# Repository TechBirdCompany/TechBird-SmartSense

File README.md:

# Introduction
TechBird-SmartSense is an IoT device with a 4-channel 12-Bit ADC, to measure up to 4 temperatures. In addition it also provides an internal temperature sensore for ambiant temperatures.

# Features
- ESP32-C6-MINI-1-N4: As module
- EEMB LP103454: 2000 mAh Lipo Battery
  - 7 days of uptime with 10 seconds time gab, and ringbuffer size of 60
- ADS1015IDGSR: 2 Differntiall or 4 Channel 12-Bit ADC
- FM24CL64B-GTR: 64 kB FRAM
- RV-3028-C7: Internal RTC
- TMP1075D: Internal Temperature Sensor
- USB Type-C for communication and charging

# Software
- Use at your own risk!
- Basic UI via USB (115200, 8, n, 1)
- Sending Data via MQTT
- Again... use at your own risk!
- Bugs are free to find, and free to fix.

# Known Bugs
## Hardware
- For some reasons, unknown to men, the LiPo Battery is necessary, to provide enough energy for initial W-LAN connection. Or maybe use a beefier USB power supply
- <span style="text-decoration:overline">WKUP</span> need to be routed to IO2

## Software
- When ringbuffer loops, one set of wrong data will be send

# Known Nuisances
- When in deep sleep, attaching USB connection won't reset the device and the lid need to be removed in order to get to the bootmenu
- Main connector is not made to be removed frequently, which makes charging pretty annoying

# Arduino IDE Setup
- The settings should look something like this:

- The following libraries shoulld be installed:
  - https://github.com/arduino-libraries/Arduino_JSON
  - https://github.com/arduino-libraries/NTPClient
  - https://github.com/adafruit/Adafruit_ADS1X15
  - https://github.com/hideakitai/DebugLog
  - https://github.com/RobTillaart/FRAM_I2C
  - https://github.com/256dpi/arduino-mqtt
  - https://github.com/constiko/RV-3028_C7-Arduino_Library
  - https://github.com/PatrickBaus/Arduino-TMP1075/tree/master
    - Needs to be installed manually

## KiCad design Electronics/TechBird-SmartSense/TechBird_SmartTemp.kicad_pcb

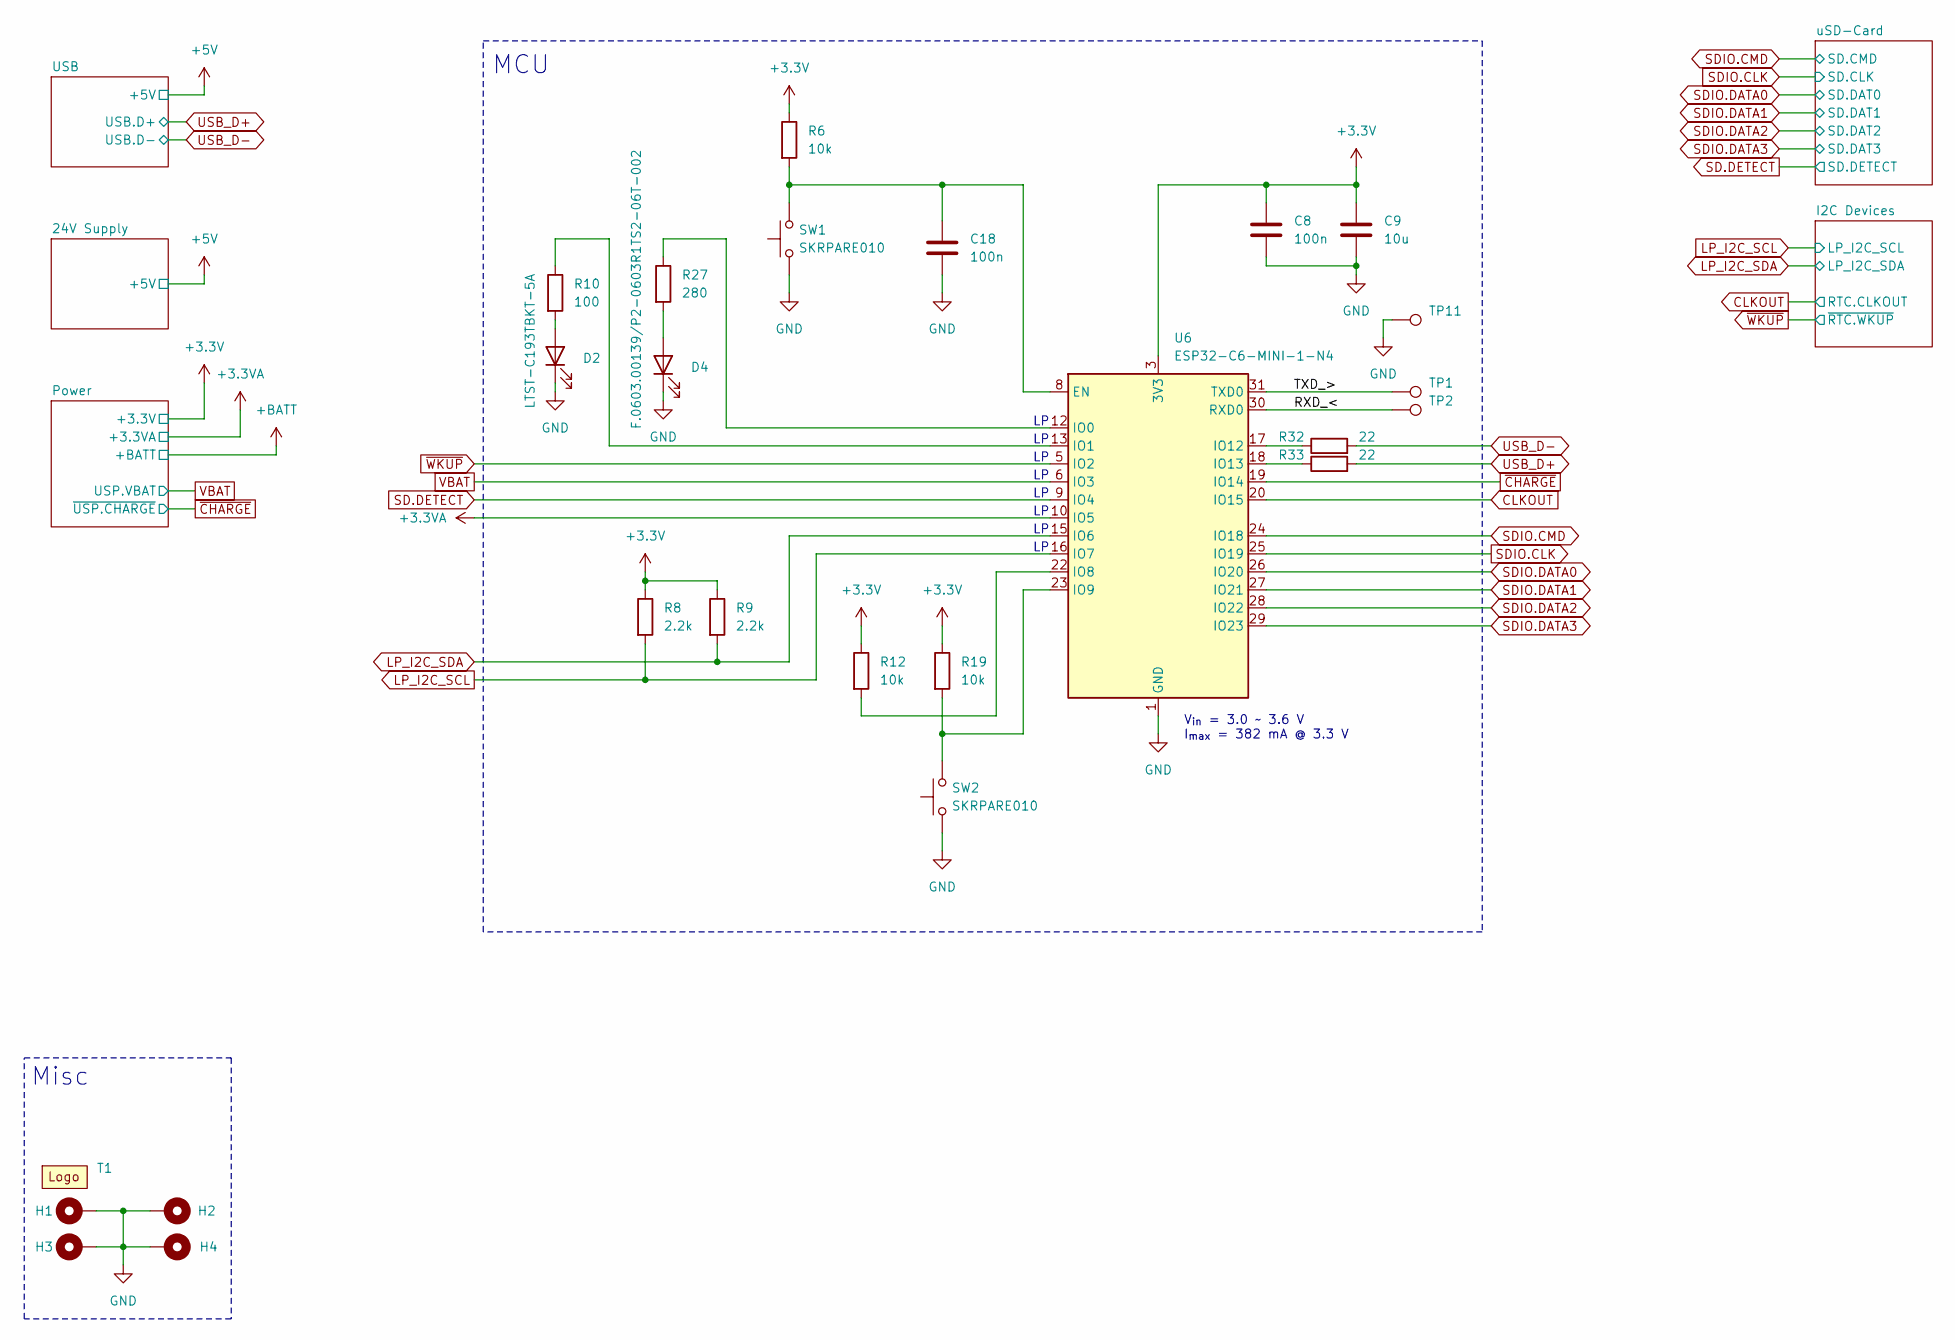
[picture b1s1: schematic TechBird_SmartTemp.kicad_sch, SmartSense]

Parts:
C8, C18: 100n; C_0603_1608Metric; MFG# C0603C104K3RACTU; DigiKey 399-C0603C104K3RACTUCT-ND
C9: 10u; C_0603_1608Metric; MFG# LMK107BBJ106MALT; DigiKey 587-3258-1-ND
D2: LTST-C193TBKT-5A; LED_0603_1608Metric; MFG# LTST-C193TBKT-5A; DigiKey 160-1827-1-ND
D4: F.0603.00139/P2-0603R1TS2-06T-002; LED_0603_1608Metric; MFG# F.0603.00139/P2-0603R1TS2-06T-002
H1, H2, H3, H4: MountingHole_Pad; MountingHole_3.2mm_M3_DIN965_Pad
R6, R12, R19: 10k; R_0603_1608Metric; MFG# RC0603FR-0710KL; DigiKey 311-10.0KHRCT-ND
R8, R9: 2.2k; R_0603_1608Metric; MFG# CRGCQ0603F2K2; DigiKey A129692CT-ND
R10: 100; R_0603_1608Metric; MFG# CRCW0603100RFKEA; DigiKey 541-100HCT-ND
R27: 280; R_0603_1608Metric; MFG# RC0603FR-07280RL; DigiKey 311-280HRCT-ND
R32, R33: 22; R_0603_1608Metric; MFG# RMCF0603FT22R0; DigiKey RMCF0603FT22R0CT-ND
SW1, SW2: SKRPARE010; SW_Push_1P1T_NO_Vertical_Wuerth_434133025816; MFG# SKRPARE010; DigiKey 4809-SKRPARE010CT-ND
T1: TechBird_Silk
TP1, TP2, TP11: TestPoint; TestPoint_Pad_D1.0mm
U6: ESP32-C6-MINI-1-N4; ESP32-C6-MINI-1; MFG# ESP32-C6-MINI-1-N4; DigiKey 1965-ESP32-C6-MINI-1-N4CT-ND

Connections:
+3.3V: C8.1, C9.1, R6.1, R8.1, R9.1, R12.1, R19.1, U6.3 (3V3); also elsewhere on the board
+3.3VA: U6.10 (IO5); also elsewhere on the board
/RXD_<: TP2.1, U6.30 (RXD0)
/TXD_>: TP1.1, U6.31 (TXD0)
CLKOUT: U6.20 (IO15); also elsewhere on the board
GND: C8.2, C9.2, C18.2, D2.1 (K), D4.1 (K), H1.1, H2.1, H3.1, H4.1, SW1.1, SW2.1, TP11.1, U6.1 (GND), U6.2 (GND), U6.11 (GND), U6.14 (GND), U6.36 (GND), U6.37 (GND), U6.38 (GND), U6.39 (GND), U6.40 (GND), U6.41 (GND), U6.42 (GND), U6.43 (GND), U6.44 (GND), U6.45 (GND), U6.46 (GND), U6.47 (GND), U6.48 (GND), U6.49 (GND), U6.50 (GND), U6.51 (GND), U6.52 (GND), U6.53 (GND); also elsewhere on the board
LP_I2C_SCL: R8.2, U6.16 (IO7); also elsewhere on the board
LP_I2C_SDA: R9.2, U6.15 (IO6); also elsewhere on the board
unnamed: D2.2 (A), R10.2
unnamed: D4.2 (A), R27.2
unnamed: C18.1, R6.2, SW1.2, U6.8 (EN)
unnamed: R27.1, U6.12 (IO0)
unnamed: R10.1, U6.13 (IO1)
unnamed: R12.2, U6.22 (IO8)
unnamed: R19.2, SW2.2, U6.23 (IO9)
unnamed: R32.1, U6.17 (IO12)
unnamed: R33.1, U6.18 (IO13)
SD.DETECT: U6.9 (IO4); also elsewhere on the board
SDIO.CLK: U6.25 (IO19); also elsewhere on the board
SDIO.CMD: U6.24 (IO18); also elsewhere on the board
SDIO.DATA0: U6.26 (IO20); also elsewhere on the board
SDIO.DATA1: U6.27 (IO21); also elsewhere on the board
SDIO.DATA2: U6.28 (IO22); also elsewhere on the board
SDIO.DATA3: U6.29 (IO23); also elsewhere on the board
USB_D+: R33.2; also elsewhere on the board
USB_D-: R32.2; also elsewhere on the board
VBAT: U6.6 (IO3); also elsewhere on the board
~CHARGE: U6.19 (IO14); also elsewhere on the board
~WKUP: U6.5 (IO2); also elsewhere on the board

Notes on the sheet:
Misc
V_{in} = 3.0 ~ 3.6 V I_{max} = 382 mA @ 3.3 V
MCU

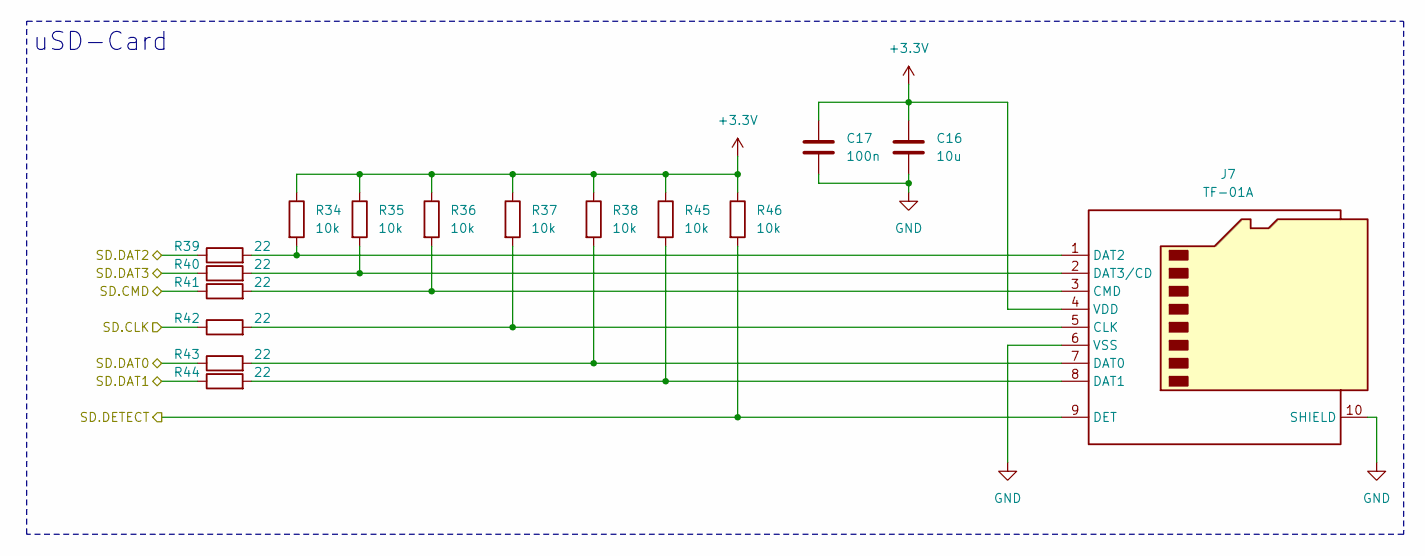
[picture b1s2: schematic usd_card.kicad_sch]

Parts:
C16: 10u; C_0603_1608Metric; MFG# LMK107BBJ106MALT; DigiKey 587-3258-1-ND
C17: 100n; C_0603_1608Metric; MFG# C0603C104K3RACTU; DigiKey 399-C0603C104K3RACTUCT-ND
J7: TF-01A; HRO TF-01A
R34, R35, R36, R37, R38, R45, R46: 10k; R_0603_1608Metric; MFG# RC0603FR-0710KL; DigiKey 311-10.0KHRCT-ND
R39, R40, R41, R42, R43, R44: 22; R_0603_1608Metric; MFG# RMCF0603FT22R0; DigiKey RMCF0603FT22R0CT-ND

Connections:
+3.3V: C16.1, C17.1, J7.4 (VDD), R34.1, R35.1, R36.1, R37.1, R38.1, R45.1, R46.1; also elsewhere on the board
GND: C16.2, C17.2, J7.6 (VSS), J7.10 (SHIELD); also elsewhere on the board
unnamed: J7.5 (CLK), R37.2, R42.2
unnamed: J7.3 (CMD), R36.2, R41.2
unnamed: J7.7 (DAT0), R38.2, R43.2
unnamed: J7.8 (DAT1), R44.2, R45.2
unnamed: J7.1 (DAT2), R34.2, R39.2
unnamed: J7.2 (DAT3/CD), R35.2, R40.2
SD.DETECT: J7.9 (DET), R46.2; also elsewhere on the board
SDIO.CLK: R42.1; also elsewhere on the board
SDIO.CMD: R41.1; also elsewhere on the board
SDIO.DATA0: R43.1; also elsewhere on the board
SDIO.DATA1: R44.1; also elsewhere on the board
SDIO.DATA2: R39.1; also elsewhere on the board
SDIO.DATA3: R40.1; also elsewhere on the board

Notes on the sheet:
uSD-Card

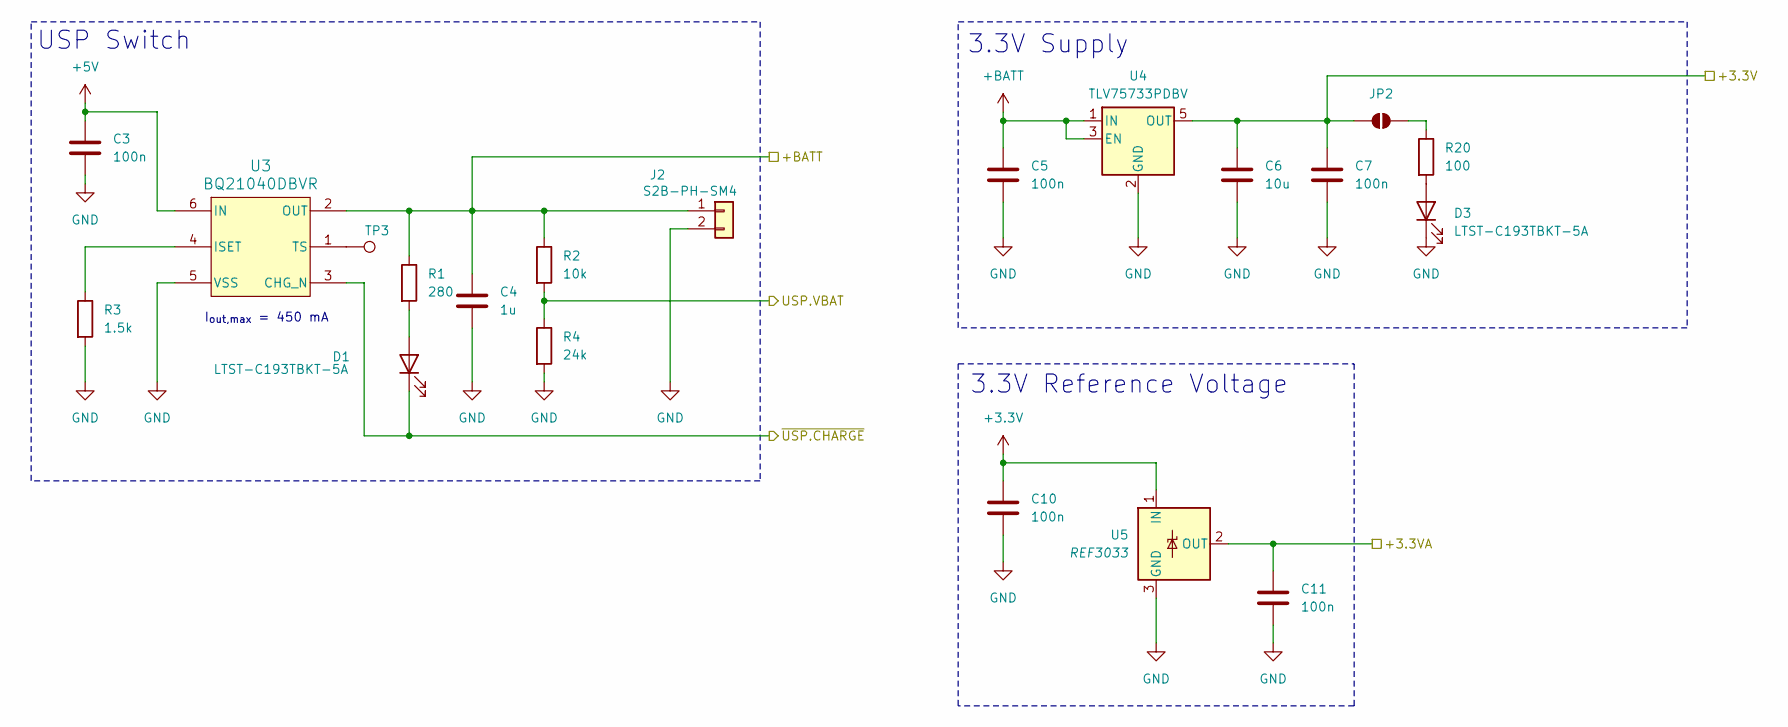
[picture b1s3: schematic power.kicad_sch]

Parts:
C3, C5, C7, C10, C11: 100n; C_0603_1608Metric; MFG# C0603C104K3RACTU; DigiKey 399-C0603C104K3RACTUCT-ND
C4: 1u; C_0603_1608Metric; MFG# C1608X7R1C105K080DC; DigiKey 445-C1608X7R1C105K080DCCT-ND
C6: 10u; C_0603_1608Metric; MFG# LMK107BBJ106MALT; DigiKey 587-3258-1-ND
D1, D3: LTST-C193TBKT-5A; LED_0603_1608Metric; MFG# LTST-C193TBKT-5A; DigiKey 160-1827-1-ND
J2: S2B-PH-SM4; JST_PH_S2B-PH-SM4-TB_1x02-1MP_P2.00mm_Horizontal; MFG# S2B-PH-SM4-TB; DigiKey 455-S2B-PH-SM4-TBCT-ND
JP2: SolderJumper_2_Open; SolderJumper-2_P1.3mm_Open_TrianglePad1.0x1.5mm
R1: 280; R_0603_1608Metric; MFG# ERJ-3EKF2800V; DigiKey P280HCT-ND
R2: 10k; R_0603_1608Metric; MFG# RC0603FR-0710KL; DigiKey 311-10.0KHRCT-ND
R3: 1.5k; R_0603_1608Metric; MFG# ERA-3AEB152V; DigiKey P1.5KDBCT-ND
R4: 24k; R_0603_1608Metric; MFG# CRCW060324K0FKEAC; DigiKey 541-5285-1-ND
R20: 100; R_0603_1608Metric; MFG# CRCW0603100RFKEA; DigiKey 541-100HCT-ND
TP3: TestPoint; TestPoint_Pad_D1.0mm
U3: BQ21040DBVR; SOT-23-6; MFG# BQ21040DBVR; DigiKey 296-47315-1-ND
U4: TLV75733PDBV; SOT-23-5; MFG# TLV75733PDBVR; DigiKey 296-50414-1-ND
U5: REF3033; SOT-23; MFG# REF3033AIDBZR; DigiKey 296-26324-1-ND

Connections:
+3.3V: C6.1, C7.1, C10.1, JP2.2 (B), U4.5 (OUT), U5.1 (IN); also elsewhere on the board
+3.3VA: C11.1, U5.2 (OUT); also elsewhere on the board
+5V: C3.1, U3.6 (IN); also elsewhere on the board
+BATT: C4.1, C5.1, J2.1, R1.1, R2.1, U3.2 (OUT), U4.1 (IN), U4.3 (EN)
GND: C3.2, C4.2, C5.2, C6.2, C7.2, C10.2, C11.2, D3.1 (K), J2.2, R3.2, R4.2, U3.5 (VSS), U4.2 (GND), U5.3 (GND); also elsewhere on the board
unnamed: D1.2 (A), R1.2
unnamed: D3.2 (A), R20.2
unnamed: JP2.1 (A), R20.1
unnamed: R3.1, U3.4 (ISET)
unnamed: TP3.1, U3.1 (TS)
VBAT: R2.2, R4.1; also elsewhere on the board
~CHARGE: D1.1 (K), U3.3 (CHG_N); also elsewhere on the board

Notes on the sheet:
I_{out,max} = 450 mA
USP Switch
3.3V Supply
3.3V Reference Voltage

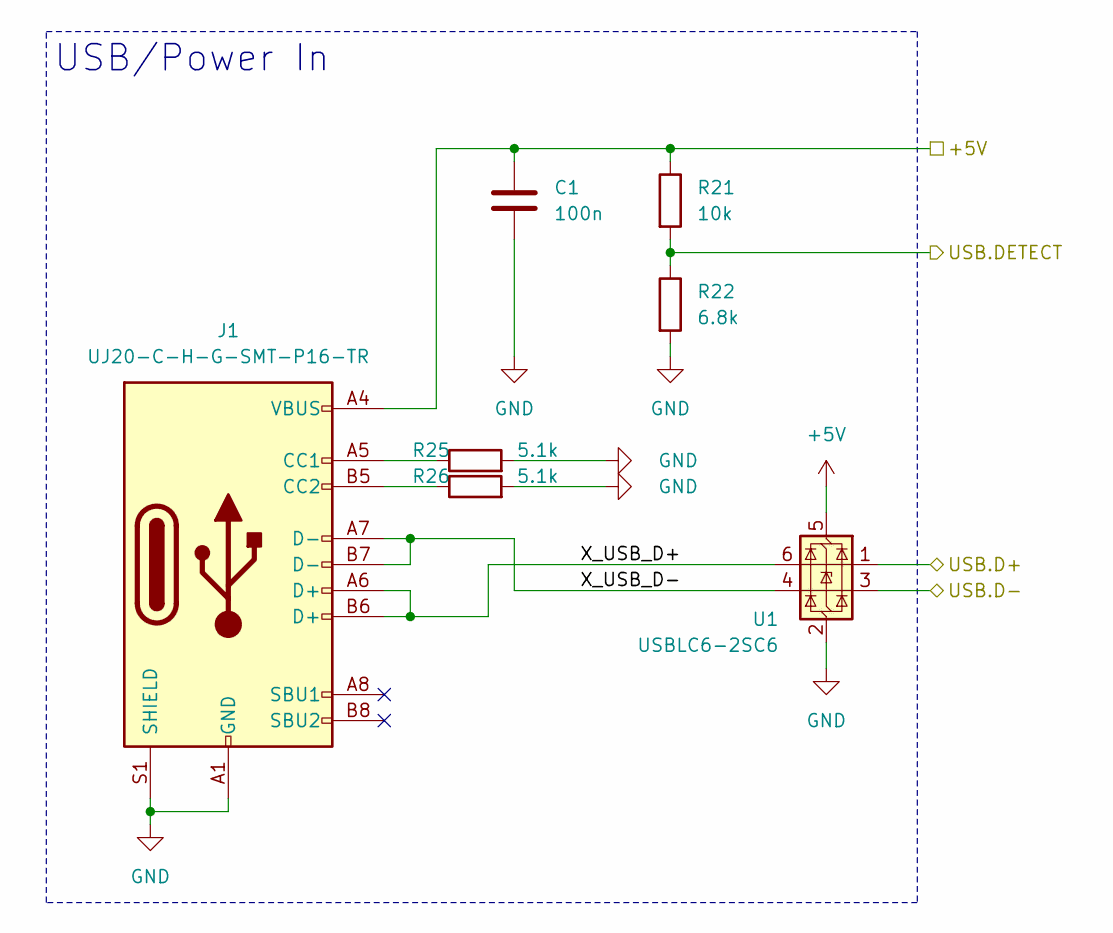
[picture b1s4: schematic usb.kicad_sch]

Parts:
C1: 100n; C_0603_1608Metric; MFG# C0603C104K3RACTU; DigiKey 399-C0603C104K3RACTUCT-ND
J1: UJ20-C-H-G-SMT-P16-TR; USB_C_Receptacle_G-Switch_GT-USB-7010ASV; MFG# UJ20-C-H-G-SMT-P16-TR; DigiKey 2223-UJ20-C-H-G-SMT-P16-TRCT-ND
R21: 10k; R_0603_1608Metric; MFG# RC0603FR-0710KL; DigiKey 311-10.0KHRCT-ND
R22: 6.8k; R_0603_1608Metric; MFG# ERJ-1GNF6801C; DigiKey P123125CT-ND
R25, R26: 5.1k; R_0603_1608Metric; MFG# RC0603FR-075K1L; DigiKey 311-5.10KHRCT-ND
U1: USBLC6-2SC6; SOT-23-6; MFG# USBLC6-2SC6; DigiKey 497-5235-1-ND

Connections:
+5V: C1.1, J1.A4 (VBUS), J1.A9 (VBUS), J1.B4 (VBUS), J1.B9 (VBUS), R21.1, U1.5 (VBUS); also elsewhere on the board
/USB/USB.DETECT: R21.2, R22.1
/USB/X_USB_D+: J1.A6 (D+), J1.B6 (D+), U1.6 (I/O1)
/USB/X_USB_D-: J1.A7 (D-), J1.B7 (D-), U1.4 (I/O2)
GND: C1.2, J1.A1 (GND), J1.A12 (GND), J1.B1 (GND), J1.B12 (GND), J1.S1 (SHIELD), R22.2, R25.2, R26.2, U1.2 (GND); also elsewhere on the board
unnamed: J1.A5 (CC1), R25.1
unnamed: J1.B5 (CC2), R26.1
USB_D+: U1.1 (I/O1); also elsewhere on the board
USB_D-: U1.3 (I/O2); also elsewhere on the board

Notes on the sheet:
USB/Power In

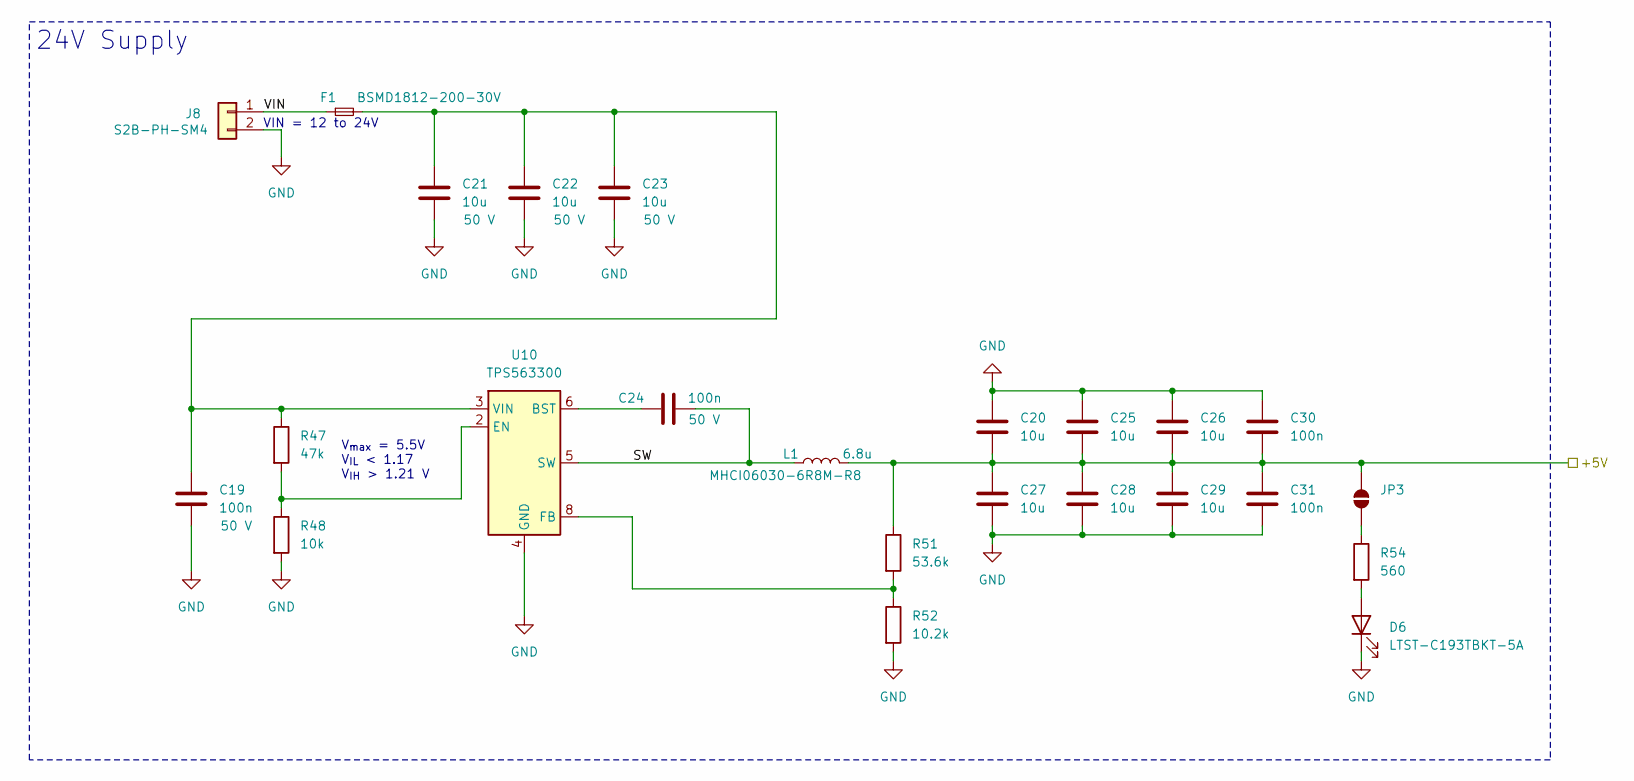
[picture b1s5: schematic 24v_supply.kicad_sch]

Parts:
C19, C24: 100n; R_0603_1608Metric; Voltage 50 V; MFG# C0603C104K5RACTU; DigiKey 399-C0603C104K5RACTUCT-ND
C20, C25, C26, C27, C28, C29: 10u; C_0603_1608Metric; MFG# LMK107BBJ106MALT; DigiKey 587-3258-1-ND
C21, C22, C23: 10u; R_0805_2012Metric; Voltage 50 V; MFG# CL31A106KBHNNNE; DigiKey 1276-2876-1-ND
C30, C31: 100n; C_0603_1608Metric; MFG# C0603C104K3RACTU; DigiKey 399-C0603C104K3RACTUCT-ND
D6: LTST-C193TBKT-5A; LED_0603_1608Metric; MFG# LTST-C193TBKT-5A; DigiKey 160-1827-1-ND
F1: BSMD1812-200-30V; Fuse_1812_4532Metric; MFG# BSMD1812-200-30V
J8: S2B-PH-SM4; JST_PH_S2B-PH-SM4-TB_1x02-1MP_P2.00mm_Horizontal; MFG# S2B-PH-SM4-TB; DigiKey 455-S2B-PH-SM4-TBCT-ND
JP3: SolderJumper_2_Open; SolderJumper-2_P1.3mm_Open_TrianglePad1.0x1.5mm
L1: 6.8u; L_Chilisin_BMRx00060630; MFG# MHCI06030-6R8M-R8
R47: 47k; R_0603_1608Metric; MFG# RC0603FR-0747KL; DigiKey 311-47.0KHRCT-ND
R48: 10k; R_0603_1608Metric; MFG# RC0603FR-0710KL; DigiKey 311-10.0KHRCT-ND
R51: 53.6k; R_0603_1608Metric; MFG# RC0603FR-0753K6L; DigiKey 311-53.6KHRCT-ND
R52: 10.2k; R_0603_1608Metric; MFG# RC0603FR-0710K2L; DigiKey 311-10.2KHRCT-ND
R54: 560; R_0603_1608Metric; MFG# 73L2R56J; DigiKey 60-73L2R56JCT-ND
U10: TPS563300; SOT-583-8; MFG# TPS563300DRLR; DigiKey 296-TPS563300DRLRCT-ND

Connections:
+5V: C20.2, C25.2, C26.2, C27.1, C28.1, C29.1, C30.2, C31.1, JP3.2 (B), L1.2, R51.1; also elsewhere on the board
/24V Supply/SW: C24.2, L1.1, U10.5 (SW)
/24V Supply/VIN: F1.1, J8.1
GND: C19.2, C20.1, C21.2, C22.2, C23.2, C25.1, C26.1, C27.2, C28.2, C29.2, C30.1, C31.2, D6.1 (K), J8.2, R48.2, R52.2, U10.4 (GND); also elsewhere on the board
unnamed: D6.2 (A), R54.2
unnamed: JP3.1 (A), R54.1
unnamed: C24.1, U10.6 (BST)
unnamed: R47.2, R48.1, U10.2 (EN)
unnamed: R51.2, R52.1, U10.8 (FB)
unnamed: C19.1, C21.1, C22.1, C23.1, F1.2, R47.1, U10.3 (VIN)

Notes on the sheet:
VIN = 12 to 24V
V_{max} = 5.5V V_{IL} < 1.17 V_{IH} > 1.21 V
24V Supply

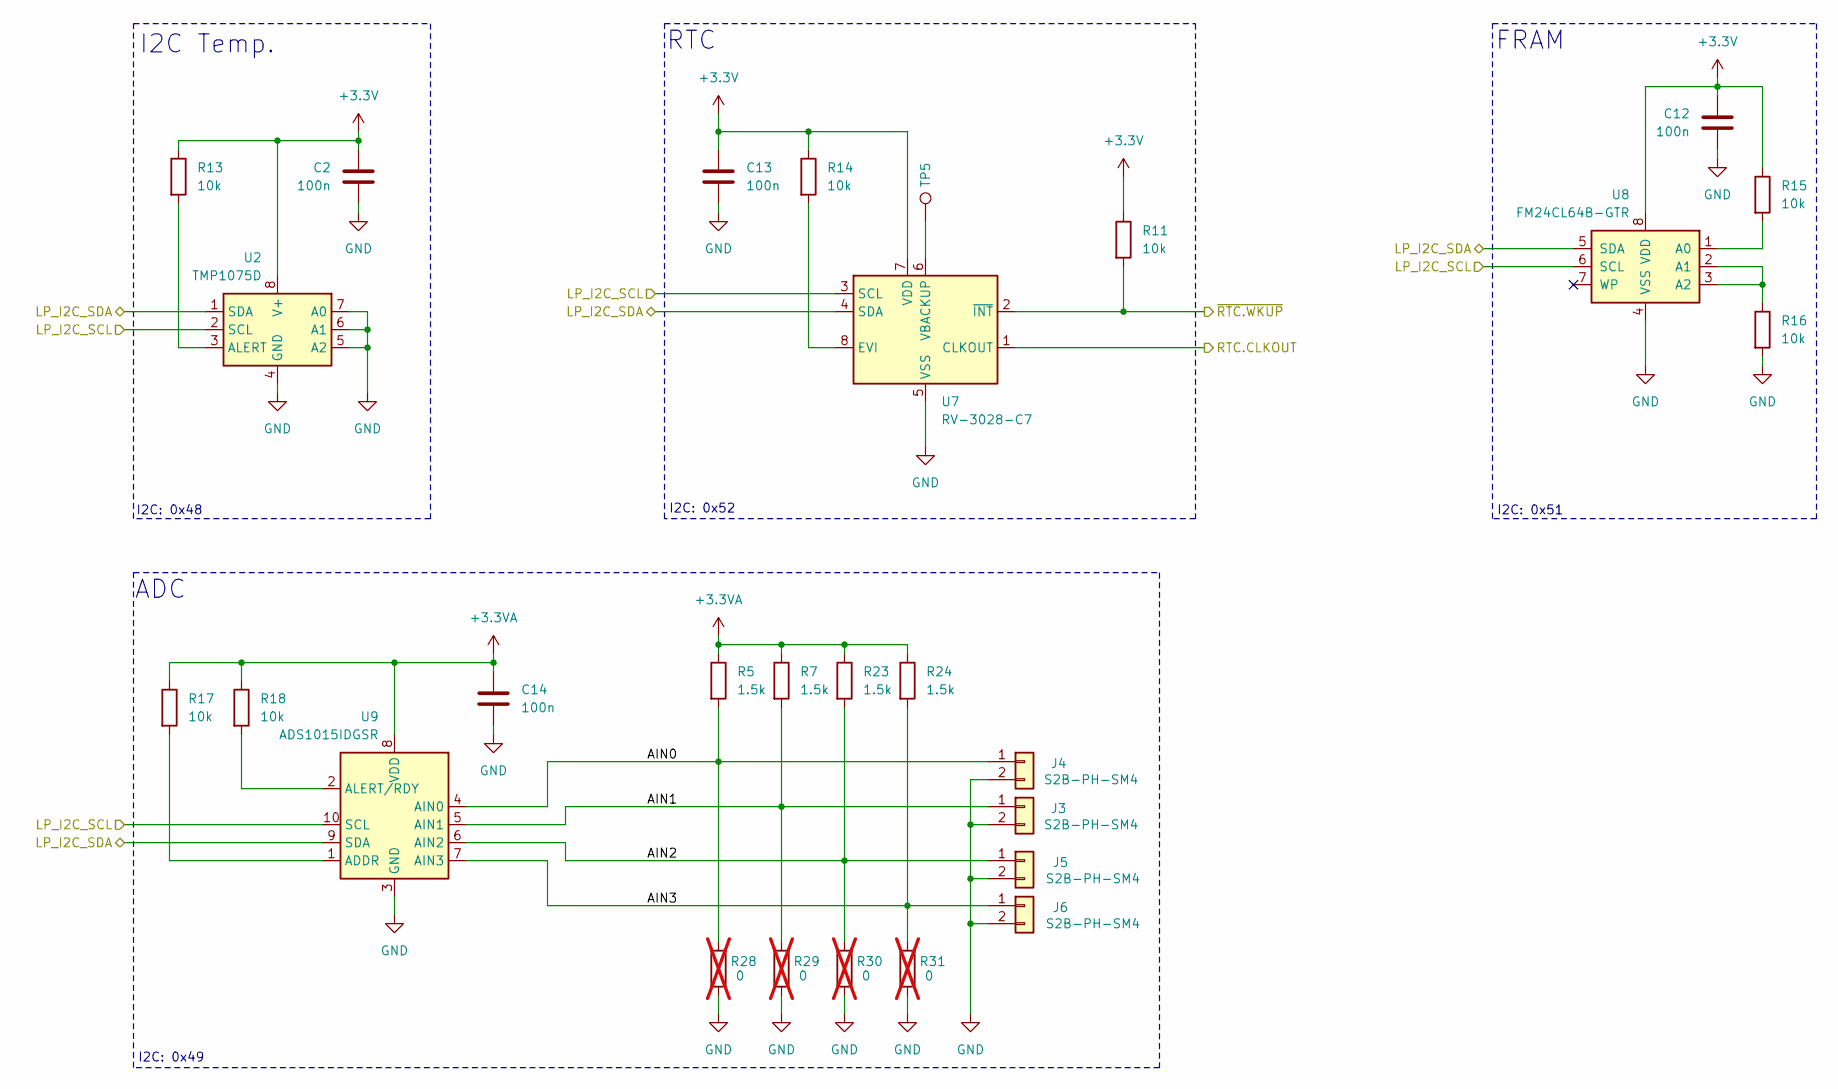
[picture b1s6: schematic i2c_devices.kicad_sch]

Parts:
C2, C12, C13, C14: 100n; C_0603_1608Metric; MFG# C0603C104K3RACTU; DigiKey 399-C0603C104K3RACTUCT-ND
J3, J4, J5, J6: S2B-PH-SM4; JST_PH_S2B-PH-SM4-TB_1x02-1MP_P2.00mm_Horizontal; MFG# S2B-PH-SM4-TB; DigiKey 455-S2B-PH-SM4-TBCT-ND
R5, R7, R23, R24: 1.5k; R_0603_1608Metric; MFG# ERA-3AEB152V; DigiKey P1.5KDBCT-ND
R11, R13, R14, R15, R16, R17, R18: 10k; R_0603_1608Metric; MFG# RC0603FR-0710KL; DigiKey 311-10.0KHRCT-ND
R28, R29, R30, R31: 0; R_0603_1608Metric; MFG# CR0603AJ/-000EAS; DigiKey CR0603AJ/-000EASCT-ND; not fitted
TP5: TestPoint; TestPoint_Pad_D1.0mm
U2: TMP1075D; SOIC-8_3.9x4.9mm_P1.27mm; MFG# TMP1075DR; DigiKey 296-51833-1-ND
U7: RV-3028-C7; MicroCrystal_C7_SON-8_1.5x3.2mm_P0.9mm; MFG# RV-3028-C7 32.768KHZ 1PPM-TA-QA; DigiKey 2195-RV-3028-C732.768KHZ1PPM-TA-QACT-ND
U8: FM24CL64B-GTR; SOIC-8_3.9x4.9mm_P1.27mm; MFG# FM24CL64B-GTR; DigiKey 448-FM24CL64B-GTRCT-ND
U9: ADS1015IDGSR; TSSOP-10_3x3mm_P0.5mm; MFG# ADS1015IDGSR; DigiKey 296-41185-1-ND

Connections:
+3.3V: C2.1, C12.1, C13.1, R11.1, R13.1, R14.1, R15.1, U2.8 (V+), U7.7 (VDD), U8.8 (VDD); also elsewhere on the board
+3.3VA: C14.1, R5.1, R7.1, R17.1, R18.1, R23.1, R24.1, U9.8 (VDD); also elsewhere on the board
/I2C Devices/AIN0: J4.1, R5.2, R28.2, U9.4 (AIN0)
/I2C Devices/AIN1: J3.1, R7.2, R29.2, U9.5 (AIN1)
/I2C Devices/AIN2: J5.1, R23.2, R30.2, U9.6 (AIN2)
/I2C Devices/AIN3: J6.1, R24.2, R31.2, U9.7 (AIN3)
CLKOUT: U7.1 (CLKOUT); also elsewhere on the board
GND: C2.2, C12.2, C13.2, C14.2, J3.2, J4.2, J5.2, J6.2, R16.2, R28.1, R29.1, R30.1, R31.1, U2.4 (GND), U2.5 (A2), U2.6 (A1), U2.7 (A0), U7.5 (VSS), U8.4 (VSS), U9.3 (GND); also elsewhere on the board
LP_I2C_SCL: U2.2 (SCL), U7.3 (SCL), U8.6 (SCL), U9.10 (SCL); also elsewhere on the board
LP_I2C_SDA: U2.1 (SDA), U7.4 (SDA), U8.5 (SDA), U9.9 (SDA); also elsewhere on the board
unnamed: R13.2, U2.3 (ALERT)
unnamed: R14.2, U7.8 (EVI)
unnamed: TP5.1, U7.6 (VBACKUP)
unnamed: R15.2, U8.1 (A0)
unnamed: R16.1, U8.2 (A1), U8.3 (A2)
unnamed: R17.2, U9.1 (ADDR)
unnamed: R18.2, U9.2 (ALERT/RDY)
~WKUP: R11.2, U7.2 (~INT); also elsewhere on the board

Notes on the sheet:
I2C: 0x49
I2C Temp.
I2C: 0x52
I2C: 0x48
FRAM
ADC
I2C: 0x51
RTC

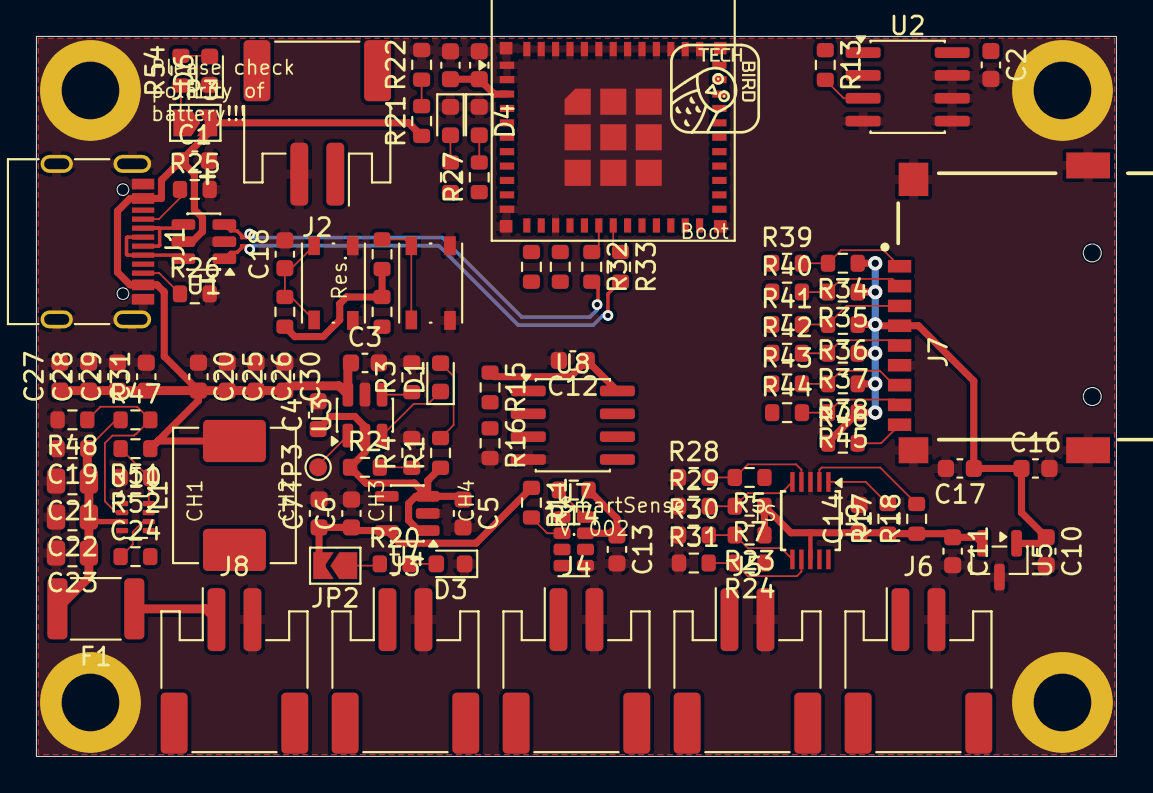
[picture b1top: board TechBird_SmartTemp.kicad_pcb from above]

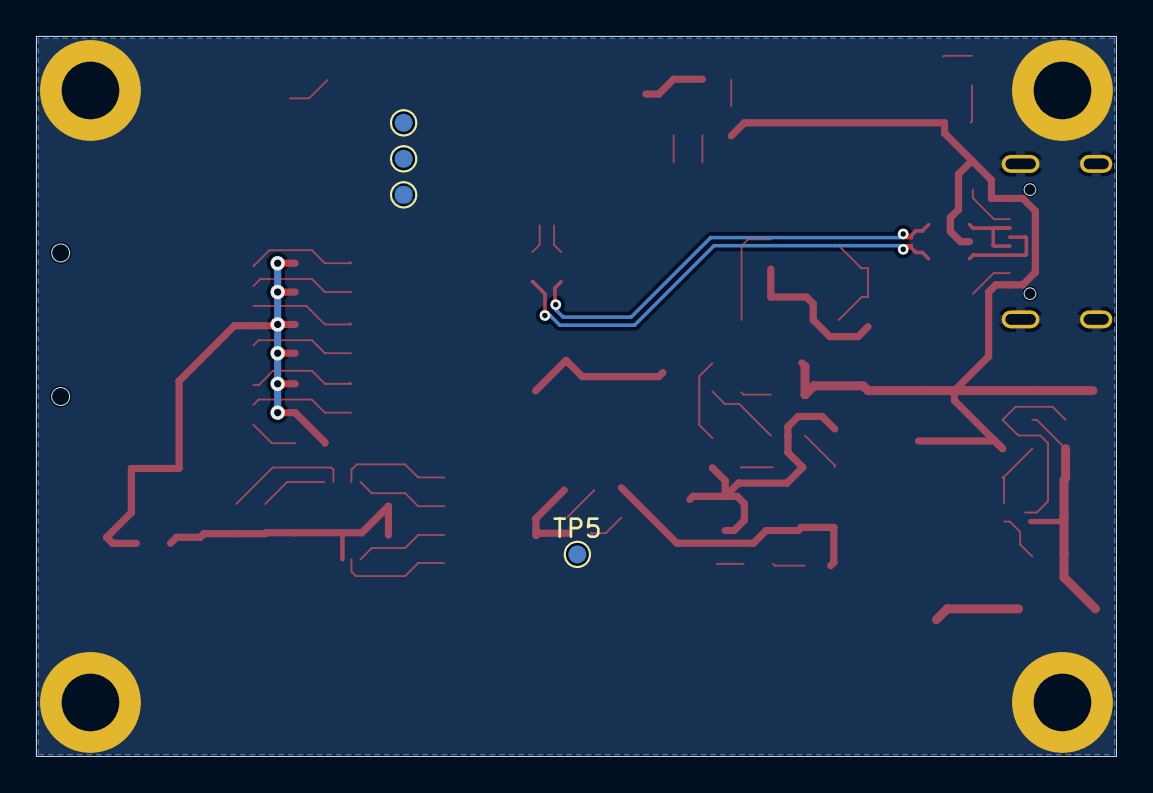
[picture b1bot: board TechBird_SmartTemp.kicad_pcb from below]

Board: 2 copper layers, 60.0 x 40.0 mm, 120 parts (4 on the bottom side), 66 nets.

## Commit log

2025-12-02 Intial Commit
    Initial Commit
2025-12-02 Create README.md
    Create README.md
2025-12-02 Changed readme.md
    Added pictures.
2025-12-02 Update README.md
    Typo
2025-12-03 Update TechBird_SmartSenseOS.ino
    Formated Debug Outputs.
2025-12-03 Changed license
2025-12-03 Update TechBird_SmartSenseOS.ino
    Added bootmenuTask, to access bootmenu during normal use. Deepsleep need to be turned off.
2025-12-03 Changed readme.md
    Added arduino setup
2025-12-06 Added single shot functionality
    Added single shot functionality, which sends directly after a certain time.
    Added check if deepsleep time is at least 10 seconds, as connecting to WiFi and MQTT needs that time.
    Currently it is not timesensitive, soooo the time between points might be bigger as you expect.
    Added used libraries to readme.md
2025-12-07 Initial Push for 003
2026-01-09 Update TechBird_SmartSenseOS.ino
    Series Resistor need to be switched to 10k. Will then measure from -35 °C to plus 40 °C or something.
2026-01-10 Update TechBird_SmartSenseOS.ino
    Fixed NTP Stuff
2026-01-11 Update TechBird_SmartSenseOS.ino
    Fixed NTP stuff.... hopefully
